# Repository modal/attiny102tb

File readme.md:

Atmel ATTINY102 Test Board
==========================

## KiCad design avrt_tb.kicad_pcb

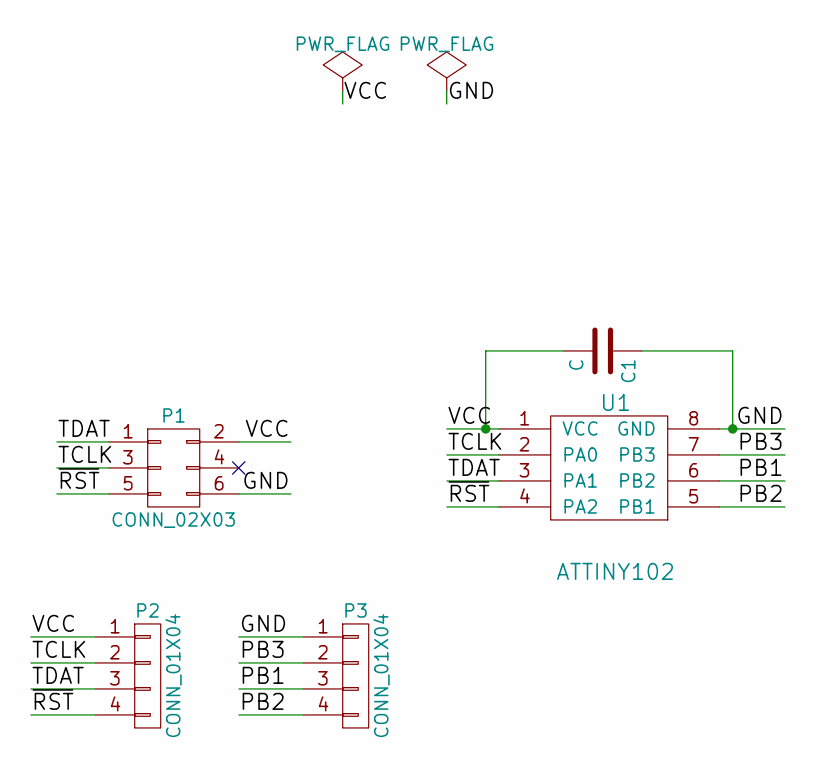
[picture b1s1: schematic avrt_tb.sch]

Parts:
C1: C; C_0805_HandSoldering
P1: CONN_02X03; Pin_Header_Straight_2x03
P2, P3: CONN_01X04; Pin_Header_Straight_1x04
U1: ATTINY102; SOIC-8-N

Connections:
/GND: C1.1, P1.6, P3.1, U1.8 (GND)
/PB1: P3.3, U1.6 (PB2)
/PB2: P3.4, U1.5 (PB1)
/PB3: P3.2, U1.7 (PB3)
/TCLK: P1.3, P2.2, U1.2 (PA0)
/TDAT: P1.1, P2.3, U1.3 (PA1)
/VCC: C1.2, P1.2, P2.1, U1.1 (VCC)
/~RST: P1.5, P2.4, U1.4 (PA2)

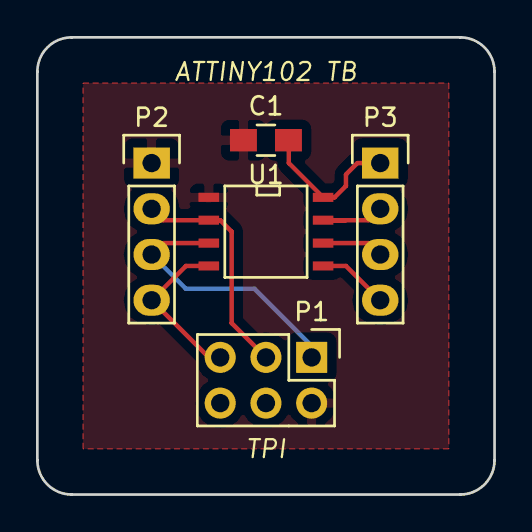
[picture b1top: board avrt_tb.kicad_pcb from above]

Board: 2 copper layers, 25.4 x 25.4 mm, 5 parts (0 on the bottom side), 8 nets.

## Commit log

2016-06-03 Initial commit for an Atmel Attiny102 board
2016-06-03 Add preliminary readme.md
2016-06-03 Add extra files to gitignore file
2016-06-03 Ignore netlist files
2016-06-03 Remove avrt_tb.net from tracked files
2016-06-03 Update output path for gerber and drill files
